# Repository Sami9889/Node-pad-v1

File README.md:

# NodePad

> A tiny, cheap, more-powerful-than-a-Pi homelab node.
> Radxa CM5 (RK3588S2, 8-core, up to 16 GB RAM) on a **100 × 100 mm** carrier board with the kind of I/O a Pi 5 doesn't give you.

**Status:** Rev 0.1 placement/connectivity audit in progress — **not fabrication-ready; do not order**. See `VERIFICATION.md` for blocking footprint and pin-mapping defects.
**Author:** Samrath "Sami" Singh
**License:** TBD (MIT or CERN-OHL-P recommended if you plan to sell it)

---

## What is it?

A carrier board for the **Radxa CM5** compute module. You skip designing the CPU/RAM/eMMC section (Radxa already did that) and get a compact server-class SBC with I/O aimed at self-hosting, homelab, mini-Kubernetes, edge servers, network appliances, and NAS-lite.

Think of it as a **"buy 4, stack them, run K3s on PoE"** kind of board.

## Why not just buy a Pi 5?

| Feature | Pi 5 | Radxa CM5 + NodePad |
|---|---|---|
| CPU | 4× Cortex-A76 @ 2.4 GHz | **8×** (4×A76 + 4×A55) @ 2.4 GHz |
| GPU | VideoCore VII | **Mali-G610 MP4** (better) |
| NPU | ❌ | **6 TOPS** |
| Max RAM | 16 GB | 16 GB |
| Ethernet | 1× **1 GbE** | 2× **2.5 GbE** |
| NVMe | via HAT | **native M.2 M-key on board** |
| PoE | HAT (~$20) | **on-board (optional-populate)** |
| Boot | microSD | **eMMC on module** (no SD lottery) |

## Killer features (the pitch)

1. **Dual 2.5 GbE** — one built into the CM5, second added via the M.2 E-key slot with a 2.5GbE controller card *or* a discrete PHY on-board. Enough to run this thing as a router or a K3s node with dedicated cluster interconnect.
2. **M.2 M-key NVMe** slot (2280) — real SSDs, no microSD.
3. **PoE+ optional** — populate the PoE PD circuit and power it with a single Ethernet cable. Leave it unpopulated for cheap builds.
4. **USB-C PD input** — programmable trigger negotiates 12V/15V/20V from any PD charger. No barrel jack, no wall wart headache.
5. **100 × 100 mm square** — cheapest JLCPCB tier, fits in a 3D-printed cube smaller than a Pi 5.

## Cost target

| Version | BOM cost (qty 10) | Sell target |
|---|---|---|
| **Base** (no PoE) | ~$40 empty board | **$99** empty / **$189** with CM5 8GB |
| **Full** (with PoE) | ~$55 empty board | **$129** empty / **$219** with CM5 8GB |

Comparable products: Turing Pi 2 ($260, but 4-node), Radxa Rock 5A ($90 SBC, no PoE/NVMe boot), DeskPi Super6C ($200, Pi CM4-only). NodePad's niche = smallest + PoE + cheap single node.

---

## Bill of Materials (JLCPCB / LCSC part numbers)

All parts picked to be **in JLCPCB's Basic or Extended library** so the whole board can be assembled by JLC PCBA (no hand-soldering headaches). Prices approximate as of 2026-07.

### Compute
| Ref | Part | Function | LCSC | Qty | Price ea. |
|---|---|---|---|---|---|
| U1 | Radxa CM5 (8 GB / 64 GB) | System-on-module | — (Radxa direct) | 1 | **$89** |
| J1, J2 | Hirose DF40C-100DS-0.4V | 2× 100-pin SoM connectors | C43880 | 2 | $2.50 |

### Networking
| Ref | Part | Function | LCSC | Qty | Price ea. |
|---|---|---|---|---|---|
| U2 | RTL8125BG | 2.5GbE MAC+PHY (2nd NIC) | C2861126 | 1 | $3.10 |
| J3, J4 | Bel Fuse 0826-1G1T-04-F | RJ45 with integrated magnetics + LEDs, PoE-capable | C516428 | 2 | $2.80 |
| Y1 | 25 MHz TCXO 3.3V 20ppm | RTL8125 clock reference | C1804 | 1 | $0.30 |

### Storage
| Ref | Part | Function | LCSC | Qty | Price ea. |
|---|---|---|---|---|---|
| J5 | M.2 M-key 2280 socket | NVMe SSD slot | C725119 | 1 | $1.20 |
| J6 | M.2 E-key 2230 socket | WiFi/BT card or 2nd NIC | C725118 | 1 | $0.95 |

### Power
| Ref | Part | Function | LCSC | Qty | Price ea. |
|---|---|---|---|---|---|
| U3 | MP2315 | 5V @ 3A buck (main rail from 12V PD) | C89358 | 1 | $0.42 |
| U4 | AP2112K-3.3 | 3.3V @ 600 mA LDO (rail for RTC, aux) | C51118 | 1 | $0.20 |
| U5 | CH224K | USB-C PD sink, programmable 5/9/12/15/20V | C970725 | 1 | $0.55 |
| U6 *(opt)* | MP8007GV | PoE+ PD converter (802.3at, 25W) | C910435 | 1 | $2.80 |
| T1 *(opt)* | 750317847 or eq. | PoE flyback transformer | C — | 1 | $2.20 |

### I/O
| Ref | Part | Function | LCSC | Qty | Price ea. |
|---|---|---|---|---|---|
| J7 | USB-C 16-pin recept. | Power in + USB 2.0 data | C165948 | 1 | $0.35 |
| J8–J11 | USB-A 3.0 vertical | 4× USB 3.0 host ports | C165999 | 4 | $0.55 |
| J12 | HDMI Type-A | HDMI 2.0 out | C2681 | 1 | $0.60 |
| J13 | 40-pin 2.54 mm header | Pi-compatible GPIO | C124378 | 1 | $0.25 |
| J14 | microSD push-push socket | Boot fallback | C91145 | 1 | $0.45 |
| J15 | 4-pin 2.54 mm header | PWM fan | C124381 | 1 | $0.15 |

### Housekeeping
| Ref | Part | Function | LCSC | Qty | Price ea. |
|---|---|---|---|---|---|
| U7 | DS3231MZ+ | I²C RTC (server needs to know time on cold boot) | C107373 | 1 | $2.10 |
| BT1 | CR2032 SMD holder | RTC coin cell | C70376 | 1 | $0.28 |
| U8, U9 | USBLC6-2SC6 | USB ESD/TVS | C7469 | 2 | $0.16 |
| SW1 | Momentary 6×6 mm tact | Reset button | C318884 | 1 | $0.08 |
| SW2 | Momentary 6×6 mm tact | Boot/recovery button | C318884 | 1 | $0.08 |
| D1–D5 | 0603 green/red LEDs | Power, activity, link, status | C72043 | 5 | $0.03 |
| — | Passives (R, C, L, ferrites) | ~120 in total, 0402/0603 | JLC Basic | — | ~$3 total |

### PCB
| Item | Spec | Price (qty 10 at JLCPCB) |
|---|---|---|
| 4-layer PCB, 100 × 100 mm, ENIG, black soldermask | Standard stackup, 1 oz Cu | ~$25 total ($2.50/board) |
| JLC PCBA (all SMD assembled) | 1-side, standard | ~$8/board |

### Rolled-up cost per finished board (qty 10)

| Version | PCB | PCBA | Components (per board) | **Empty PCB total** | Add CM5 8GB | **All-in** |
|---|---|---|---|---|---|---|
| Base (no PoE) | $2.50 | $8 | ~$26 | **~$36.50** | +$89 | **$125.50** |
| Full (with PoE) | $2.50 | $9 | ~$32 | **~$43.50** | +$89 | **$132.50** |

Room to sell base @ **$99 (empty PCB only)** or **$199 (with 8GB CM5 pre-installed)** and still keep ~40% margin. 🎯

---

## Block diagram

```
                        ┌──────────────────────────────────┐
                        │      Radxa CM5 (RK3588S2)        │
                        │  8-core • 8GB LPDDR4X • 64GB eMMC│
                        │  Native: 1 GbE, HDMI, USB3.0,    │
                        │  PCIe 2.1 x1, MIPI-DSI/CSI, GPIO │
                        └──┬───┬───┬───┬───┬───┬───┬───────┘
                           │   │   │   │   │   │   │
              ┌────────────┘   │   │   │   │   │   └──────────────┐
              │                │   │   │   │   │                  │
        ┌─────▼─────┐    ┌─────▼─┐ │   │   │ ┌─▼──────┐   ┌───────▼─────┐
        │ RTL8125BG │    │ RJ45  │ │   │   │ │ HDMI 2.0│   │ 40-pin GPIO │
        │  2.5 GbE  │◄──►│ #1 PoE│ │   │   │ └─────────┘   │  Pi-compat  │
        │  (2nd NIC)│    │ 1 GbE │ │   │   │               └─────────────┘
        └─────┬─────┘    └───────┘ │   │   │
              │                    │   │   │
         ┌────▼────┐            ┌──▼─┐ │  ┌▼─────────┐
         │  RJ45 #2│            │M.2 │ │  │ 4× USB   │
         │ 2.5 GbE │            │E-key│ │  │ 3.0 A   │
         │ (opt PoE│            │2230 │ │  └──────────┘
         │  input) │            │(WiFi│ │
         └────┬────┘            │/NIC)│ │
              │                 └─────┘ │
         ┌────▼──────┐         ┌────────▼─┐
         │ MP8007 PoE│         │ M.2 M-key│
         │  PD (opt) │         │  2280    │
         └────┬──────┘         │  NVMe    │
              │                └──────────┘
        ┌─────▼─────┐    ┌──────────────┐   ┌───────────┐
        │ CH224K PD │◄───│  USB-C in    │   │ DS3231 RTC│
        │  trigger  │    │ (5/12/20V)   │   │ +CR2032   │
        └─────┬─────┘    └──────────────┘   └───────────┘
              │
        ┌─────▼──────┐
        │ MP2315 buck│──► 5V rail (CM5, USB, fan, etc.)
        │ + AP2112   │──► 3.3V aux (RTC, LEDs, logic)
        └────────────┘
```

## Repo layout (planned)

```
nodepad/
├── README.md                (this file)
├── DESIGN.md                (deep design rationale, pin assignments, DRC rules)
├── BOM.csv                  (machine-readable, for JLC PCBA upload)
├── PCB/                     (KiCad 10 project)
│   ├── NodePad.kicad_pro
│   ├── NodePad.kicad_sch    (multi-sheet: cpu, network, power, io)
│   └── NodePad.kicad_pcb
├── CAD/                     (case: front, back, mount plate)
│   └── nodepad-case.step
├── Production/
│   ├── gerbers.zip
│   ├── bom.csv              (JLC PCBA format)
│   ├── cpl.csv              (component placement)
│   └── assembly-drawings.pdf
├── Firmware/                (bootloader configs, device tree overlay if needed)
└── docs/
    └── quick-start.md
```

---

## Two variants

| | **NodePad** (base) | **NodePad-Net** (networking) |
|---|---|---|
| **Compute** | Radxa CM5 (8-core RK3588S2 + Mali-G610 GPU + 6 TOPS NPU) | Same |
| **Ethernet** | 1× 1 GbE (native) + 1× 2.5 GbE (RTL8125) | 1× 1 GbE + **2× 2.5 GbE** (2× RTL8125) |
| **Fiber** | — | **1× SFP cage** (1G SGMII) |
| **NVMe** | 1× M.2 M-key 2280 | 1× M.2 M-key 2280 |
| **WiFi slot** | 1× M.2 E-key 2230 | ❌ (PCIe1 used for 2nd NIC) |
| **HDMI** | 1× HDMI 2.0 | ❌ (headless appliance) |
| **USB** | 4× USB-A 3.0 (GL3523 hub) | 2× USB-A 3.0 |
| **PoE** | Footprint-only (DNP) | Footprint-only (DNP) |
| **Netlist stats** | 230 comps, 239 nets, 0 ERC errors | 219 comps, 227 nets, 0 ERC errors |
| **Sell target** | $99 empty / $199 with CM5 | $129 empty / $229 with CM5 |

Both share the same 100 × 100 mm 4-layer PCB scaffold; the SKiDL blocks
compose differently to build each variant's netlist.

### About the CPU + GPU

The CPU (8-core Cortex-A76/A55) and GPU (Mali-G610 MP4) live **on the
Radxa CM5 module itself** — we don't design them into the carrier
board. That's the entire point of using a SoM: you buy the pre-built
compute module for $89 and skip the ~$1000-per-chip BGA design effort.
The carrier board's job is just to break out the CM5's I/O to the
connectors, feed it power, and add the peripherals (Ethernet, USB,
NVMe, SFP, etc.).

---

| # | Decision | Choice |
|---|---|---|
| 1 | **PoE** | Footprint-only (populate optional) |
| 2 | **HDMI** | Kept |
| 3 | **2nd 2.5 GbE NIC** | On-board RTL8125BG (biggest diff vs Pi 5) |
| 4 | **USB 3.0 ports** | 4× vertical Type-A (via GL3523 hub) |
| 5 | **License** | CERN-OHL-P v2 |

---

## Next steps (in order)

- [x] Design brief locked
- [x] KiCad 10 project scaffold created (`/PCB/NodePad.kicad_pro`, `.kicad_sch`, `.kicad_pcb`)
- [x] 100 × 100 mm board outline with 4× M2.5 mounting holes
- [x] 4-layer stackup + JLC-tuned design rules + net classes (PCIe / USB3 / Ethernet / HDMI / Power)
- [x] BOM.csv with LCSC part numbers
- [x] LICENSE (CERN-OHL-P v2)
- [ ] Schematic capture — power tree
- [ ] Schematic capture — CM5 SoM connectors + decoupling
- [ ] Schematic capture — RTL8125 NIC + magnetics
- [ ] Schematic capture — M.2 M-key + E-key slots
- [ ] Schematic capture — GL3523 USB 3.0 hub + 4× USB-A
- [ ] Schematic capture — HDMI, GPIO header, RTC, buttons, LEDs
- [ ] Schematic capture — PoE section (footprint-only, DNP)
- [ ] ERC clean
- [ ] Footprint assignment (JLC-Basic priority)
- [ ] PCB placement
- [ ] PCB routing (PCIe → USB3 → HDMI → Ethernet → GPIO)
- [ ] DRC clean
- [ ] Gerber + CPL + BOM export
- [ ] Order 5 prototypes from JLCPCB (~$400)
- [ ] Bring-up + rev 2 fixes
- [ ] Sellable rev 2 spin

Realistic total timeline from your side: **~3 months part-time** to a rev-2 sellable board. My share (design + docs) is front-loaded in the first 2–3 weeks.

---

## Honest disclaimer

I can draft the schematic + rough PCB layout in KiCad and give you a starting point you can iterate on. **High-speed routing (2.5GbE differential pairs, PCIe Gen 2, USB 3.0)** benefits massively from human review before you spend money on prototypes — it's not the kind of thing to click "generate" and ship. Plan for at least **one rev-2 spin** to fix the bugs the first prototype reveals. Every serious hardware product does this.

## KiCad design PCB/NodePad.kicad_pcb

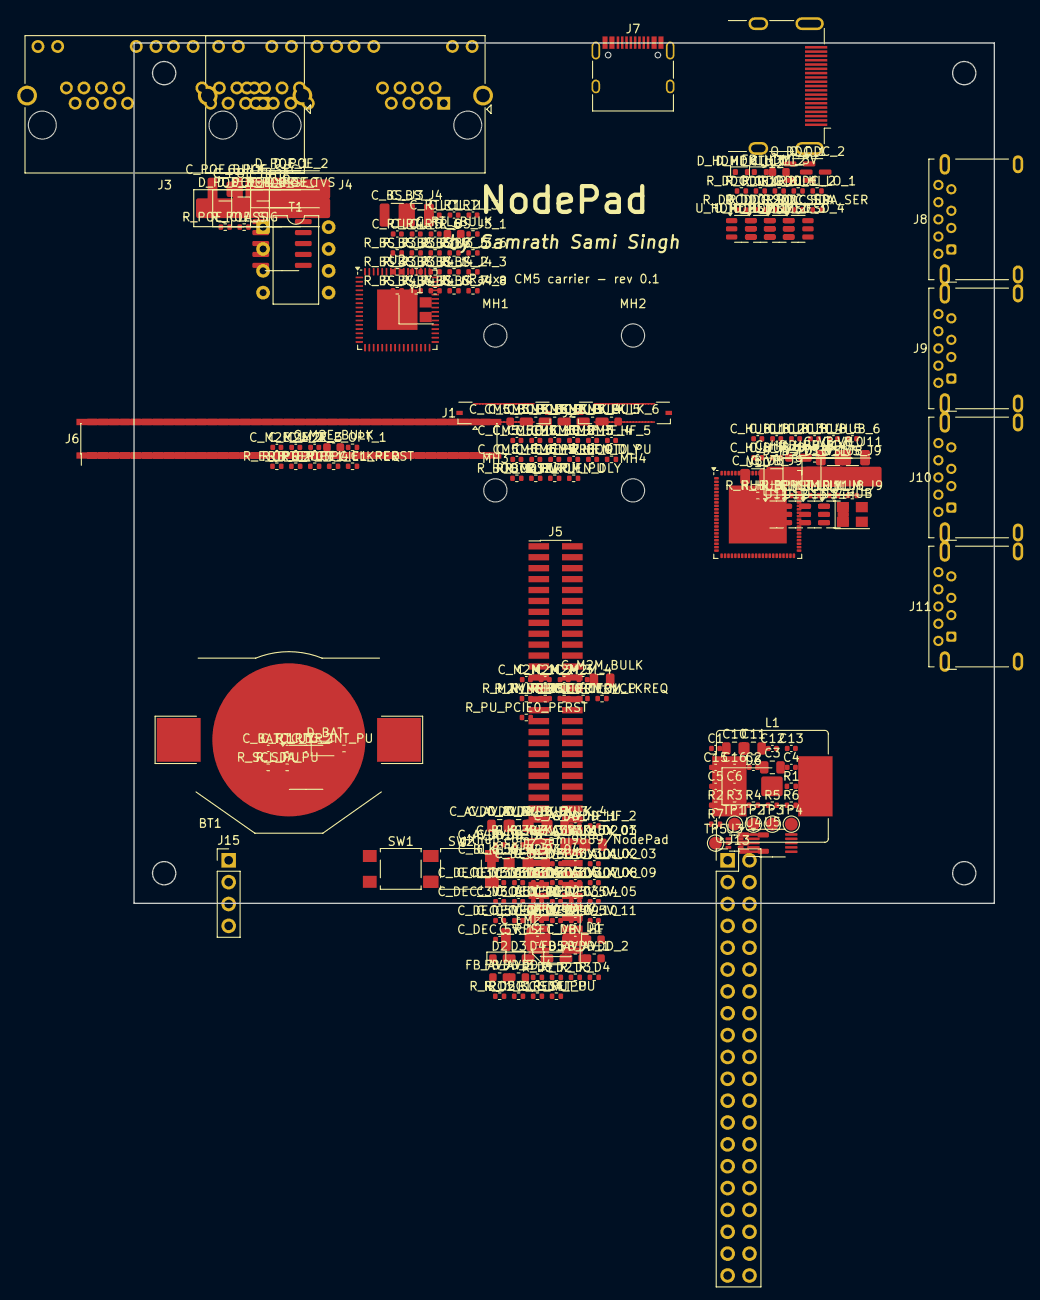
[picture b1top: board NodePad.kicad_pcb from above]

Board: 4 copper layers, 100.0 x 100.0 mm, 249 parts (0 on the bottom side), 94 nets, no tracks yet.

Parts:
BT1: CR2032; BatteryHolder_Keystone_3002_1x2032
C1, C2, C15, C16: 1uF; C_0402_1005Metric
C3, C10, C11: 22uF/25V; C_0805_2012Metric
C4, C13: 100nF; C_0402_1005Metric
C5: 2.2nF; C_0402_1005Metric
C6: 100pF; C_0402_1005Metric
C12: 10uF/16V; C_0402_1005Metric
C_AVDD_BULK_1, C_AVDD_BULK_2, C_AVDD_BULK_3, C_AVDD_BULK_4: 10uF; C_0805_2012Metric
C_AVDD_HF_1, C_AVDD_HF_2, C_AVDD_HF_3, C_AVDD_HF_4: 100nF; C_0402_1005Metric
C_BAT_1: 100nF; C_0402_1005Metric
C_BLK_3V3_AUX_01, C_BLK_3V3_AUX_02, C_BLK_3V3_AUX_03, C_BLK_5V_01, C_BLK_5V_02, C_BLK_5V_03, C_BLK_5V_04: 10uF; C_0805_2012Metric
C_BS_J3, C_BS_J4: 1nF/2kV; C_1210_3225Metric
C_CM5_BULK_1, C_CM5_BULK_2, C_CM5_BULK_3, C_CM5_BULK_4, C_CM5_BULK_5, C_CM5_BULK_6: 10uF; C_0603_1608Metric
C_CM5_HF_1, C_CM5_HF_2, C_CM5_HF_3, C_CM5_HF_4, C_CM5_HF_5, C_CM5_HF_6, C_CM5_HF_7, C_CM5_HF_8, C_CM5_HF_9, C_CM5_HF_10: 100nF; C_0402_1005Metric
C_DEC_3V3_AUX_01, C_DEC_3V3_AUX_02, C_DEC_3V3_AUX_03, C_DEC_3V3_AUX_04, C_DEC_3V3_AUX_05, C_DEC_3V3_AUX_06, C_DEC_3V3_AUX_07, C_DEC_3V3_AUX_08, C_DEC_3V3_AUX_09, C_DEC_3V3_AUX_10, C_DEC_5V_01, C_DEC_5V_02, C_DEC_5V_03, C_DEC_5V_04, C_DEC_5V_05, C_DEC_5V_06, C_DEC_5V_07, C_DEC_5V_08, C_DEC_5V_09, C_DEC_5V_10, C_DEC_5V_11, C_DEC_5V_12: 100nF; C_0402_1005Metric
C_EMI: 1nF/2kV; C_1210_3225Metric
C_HUB_1, C_HUB_2, C_HUB_3, C_HUB_4, C_HUB_5, C_HUB_6, C_HUB_7, C_HUB_8: 100nF; C_0402_1005Metric
C_HUB_BULK: 10uF; C_0603_1608Metric
C_HUB_LDO: 4.7uF; C_0603_1608Metric
C_M2E_1, C_M2E_2, C_M2E_3, C_M2M_1, C_M2M_2, C_M2M_3, C_M2M_4: 100nF; C_0402_1005Metric
C_M2E_BULK: 10uF; C_0603_1608Metric
C_M2M_BULK: 22uF/6.3V; C_0805_2012Metric
C_POE_BULK: 22uF/100V DNP; C_1210_3225Metric
C_POE_HF: 100nF/100V DNP; C_1206_3216Metric
C_POE_SEC: 47uF/25V DNP; C_1210_3225Metric
C_PWR_EN_DLY: 470nF; C_0402_1005Metric
C_RESET_DB: 100nF; C_0402_1005Metric
C_RTC_1: 100nF; C_0402_1005Metric
C_RTC_2: 1uF; C_0402_1005Metric
C_RTL_1, C_RTL_2, C_RTL_3, C_RTL_4, C_RTL_5, C_RTL_6: 100nF; C_0402_1005Metric
C_RTL_BULK: 10uF; C_0603_1608Metric
C_VB_J8, C_VB_J9, C_VB_J10, C_VB_J11: 150uF/6.3V; C_1206_3216Metric
C_VIN_BULK: 47uF/25V; CP_Elec_5x5.4
C_VIN_HF: 100nF; C_0402_1005Metric
D1: Green; LED_0603_1608Metric
D2: Blue; LED_0603_1608Metric
D3, D4: Yellow; LED_0603_1608Metric
D5: Red; LED_0603_1608Metric
D6: SMBJ12A; D_SMB
D_BAT: BAT54; D_SOD-323
D_HDMI_CTL_1, D_HDMI_CTL_2: ESD5Z5.0; D_SOD-523
D_POE_1, D_POE_2, D_POE_3, D_POE_4: HD01-T DNP; D_SMB
D_POE_OR: SS36 DNP; D_SMB
D_POE_SEC: SS36 DNP; D_SMB
D_POE_TVS: SMBJ58A DNP; D_SMB
D_TVS_J8, D_TVS_J9, D_TVS_J10, D_TVS_J11: SMBJ5.0A; D_SMB
FB_AVDD_1, FB_AVDD_2, FB_AVDD_3, FB_AVDD_4: 600R@100MHz; L_0603_1608Metric
FB_HDMI_5V: 600R@100MHz; L_0603_1608Metric
J1: CM5-J1; Hirose_BM24_BM24-40DS-2-0.35V_2x20_P0.35mm_PowerPin2_Vertic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
J2: CM5-J2; Hirose_BM24_BM24-40DS-2-0.35V_2x20_P0.35mm_PowerPin2_Vertic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
J3, J4: RJ45; RJ45_Amphenol_RJHSE538X-02
J5: M.2 M-key 2280; PinHeader_2x38_P1.27mm_Vertical_SMD
J6: M.2 E-key 2230; PinHeader_2x38_P1.27mm_Vertical_SMD
J7: USB-C; USB_C_Receptacle_HRO_TYPE-C-31-M-12
J8, J9, J10, J11: USB3-A; USB3_A_Molex_48393-001
J12: HDMI; HDMI_A_Molex_208658-1001_Horizontal
J13: GPIO40; PinHeader_2x20_P2.54mm_Vertical
J15: Fan; PinHeader_1x04_P2.54mm_Vertical
L1: 4.7uH/3A; L_Bourns_SRR1208_12.7x12.7mm
MH1, MH2, MH3, MH4: M2.5 heatsink; MountingHole_2.7mm_M2.5
Q_DDC_1, Q_DDC_2: BSS138; SOT-23
R1, R2, R6, R7: 10k; R_0402_1005Metric
R3: 0; R_0402_1005Metric
R4: 100k; R_0402_1005Metric
R5: 52.3k; R_0402_1005Metric
R_BOOT0_PU, R_BOOT1_PU, R_BOOT2_PU: 10k; R_0402_1005Metric
R_BS_J3_1, R_BS_J3_2, R_BS_J3_3, R_BS_J3_4, R_BS_J3_5, R_BS_J3_6, R_BS_J3_7, R_BS_J3_8, R_BS_J4_1, R_BS_J4_2, R_BS_J4_3, R_BS_J4_4, R_BS_J4_5, R_BS_J4_6, R_BS_J4_7, R_BS_J4_8: 75; R_0402_1005Metric
R_D1, R_D2, R_D3, R_D4, R_D5: 1k; R_0402_1005Metric
R_DDC_G_1, R_DDC_G_2: 10k; R_0402_1005Metric
R_DDC_HI_1, R_DDC_HI_2: 10k; R_0402_1005Metric
R_DDC_LO_1, R_DDC_LO_2: 10k; R_0402_1005Metric
R_DDC_SCL: 2.2k; R_0402_1005Metric
R_DDC_SCL_SER: 100; R_0402_1005Metric
R_DDC_SDA: 2.2k; R_0402_1005Metric
R_DDC_SDA_SER: 100; R_0402_1005Metric
R_E_OPT_1, R_E_OPT_2, R_E_OPT_3, R_E_OPT_4: 0/DNP; R_0402_1005Metric
R_HUB_BP: 10k; R_0402_1005Metric
R_HUB_RST: 10k; R_0402_1005Metric
R_I2C1_SCL_PU, R_I2C1_SDA_PU: 4.7k; R_0402_1005Metric
R_ILIM_J8, R_ILIM_J9, R_ILIM_J10, R_ILIM_J11: 30k; R_0402_1005Metric
R_INT_PU: 10k; R_0402_1005Metric
R_M2M_PERST: 10k; R_0402_1005Metric
R_MASKROM_PU: 10k; R_0402_1005Metric
R_NVME_ACT_PU: 10k; R_0402_1005Metric
R_PCIE0_TERM_N, R_PCIE0_TERM_P: 49.9 DNP; R_0402_1005Metric
R_POE_CLASS: 12.5 DNP; R_0402_1005Metric
R_POE_SIG: 25k DNP; R_0402_1005Metric
R_PU_PCIE0_CLKREQ, R_PU_PCIE0_PERST, R_PU_PCIE1_CLKREQ, R_PU_PCIE1_PERST: 10k; R_0402_1005Metric
R_PWR_EN_DLY: 100k; R_0402_1005Metric
R_RESET_PU: 10k; R_0402_1005Metric
R_SCL_PU: 4.7k; R_0402_1005Metric
R_SDA_PU: 4.7k; R_0402_1005Metric
SW1: RESET; SW_SPST_TL3305A
SW2: BOOT; SW_SPST_TL3305A
T1: 750317847 DNP; DIP-8_W7.62mm
TP1, TP2, TP3, TP4, TP5: TP; TestPoint_Pad_D1.5mm
U2: RTL8125BG; QFN-64-1EP_9x9mm_P0.5mm_EP4.7x4.7mm
U3: MP2315; SOT-563
U4: AP2112K-3.3; SOT-23-5
U5: CH224K; VSSOP-10_3x3mm_P0.5mm
U6: MP8007 DNP; SOIC-16_3.9x9.9mm_P1.27mm
U7: DS3231MZ+; SOIC-8_3.9x4.9mm_P1.27mm
U10: GL3523; ArtInChip_QFN-88-1EP_10x10mm_P0.4mm_EP6.74x6.74mm
U11, U12, U13, U14: TPS2553; SOT-23-6
U_HDMI_ESD_1, U_HDMI_ESD_2, U_HDMI_ESD_3, U_HDMI_ESD_4: USBLC6-2SC6; SOT-23-6
Y1: 25MHz TCXO; Crystal_SMD_3225-4Pin_3.2x2.5mm
Y_HUB: 25MHz; Crystal_SMD_3225-4Pin_3.2x2.5mm

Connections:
+3V3_AUX: C_BLK_3V3_AUX_01.1, C_BLK_3V3_AUX_02.1, C_BLK_3V3_AUX_03.1, C_DEC_3V3_AUX_01.1, C_DEC_3V3_AUX_02.1, C_DEC_3V3_AUX_03.1, C_DEC_3V3_AUX_04.1, C_DEC_3V3_AUX_05.1, C_DEC_3V3_AUX_06.1, C_DEC_3V3_AUX_07.1, C_DEC_3V3_AUX_08.1, C_DEC_3V3_AUX_09.1, C_DEC_3V3_AUX_10.1, C_HUB_1.1, C_HUB_2.1, C_HUB_3.1, C_HUB_4.1, C_HUB_5.1, C_HUB_6.1, C_HUB_7.1, C_HUB_8.1, C_HUB_BULK.1, C_M2E_1.1, C_M2E_2.1, C_M2E_3.1, C_M2E_BULK.1, C_M2M_1.1, C_M2M_2.1, C_M2M_3.1, C_M2M_4.1, C_M2M_BULK.1, C_RTC_1.1, C_RTC_2.1, C_RTL_1.1, C_RTL_2.1, C_RTL_3.1, C_RTL_4.1, C_RTL_5.1, C_RTL_6.1, C_RTL_BULK.1, D1.1, FB_AVDD_1.1, FB_AVDD_2.1, FB_AVDD_3.1, FB_AVDD_4.1, J5.69, J5.71, J5.73, J5.75, J6.2, J6.4, J6.72, J6.74, J13.1, J13.17, R_BOOT0_PU.1, R_BOOT1_PU.1, R_BOOT2_PU.1, R_DDC_G_1.1, R_DDC_G_2.1, R_DDC_LO_1.1, R_DDC_LO_2.1, R_HUB_BP.1, R_HUB_RST.1, R_I2C1_SCL_PU.1, R_I2C1_SDA_PU.1, R_INT_PU.1, R_M2M_PERST.1, R_MASKROM_PU.1, R_NVME_ACT_PU.1, R_PU_PCIE0_CLKREQ.1, R_PU_PCIE0_PERST.1, R_PU_PCIE1_CLKREQ.1, R_PU_PCIE1_PERST.1, R_RESET_PU.1, R_SCL_PU.1, R_SDA_PU.1, U2.22, U2.23, U2.30, U2.31, U2.40, U2.41, U2.50, U2.51, U7.2
+3V3_AUX1: C16.1, TP4.1, U4.5
+5V: C_BLK_5V_01.1, C_BLK_5V_02.1, C_BLK_5V_03.1, C_BLK_5V_04.1, C_CM5_BULK_1.1, C_CM5_BULK_2.1, C_CM5_BULK_3.1, C_CM5_BULK_4.1, C_CM5_BULK_5.1, C_CM5_BULK_6.1, C_CM5_HF_1.1, C_CM5_HF_2.1, C_CM5_HF_3.1, C_CM5_HF_4.1, C_CM5_HF_5.1, C_CM5_HF_6.1, C_CM5_HF_7.1, C_CM5_HF_8.1, C_CM5_HF_9.1, C_CM5_HF_10.1, C_DEC_5V_01.1, C_DEC_5V_02.1, C_DEC_5V_03.1, C_DEC_5V_04.1, C_DEC_5V_05.1, C_DEC_5V_06.1, C_DEC_5V_07.1, C_DEC_5V_08.1, C_DEC_5V_09.1, C_DEC_5V_10.1, C_DEC_5V_11.1, C_DEC_5V_12.1, FB_HDMI_5V.1, J13.2, J13.4, J15.2, R_DDC_HI_1.1, R_DDC_HI_2.1, R_DDC_SCL.1, R_DDC_SDA.1, R_PWR_EN_DLY.1, U11.1, U11.3, U12.1, U12.3, U13.1, U13.3, U14.1, U14.3, U_HDMI_ESD_1.5, U_HDMI_ESD_2.5, U_HDMI_ESD_3.5, U_HDMI_ESD_4.5
+5V1: C10.1, C11.1, C12.1, C13.1, C15.1, L1.2, R5.1, TP3.1, U4.1, U4.3
BOBSMITH_J3: C_BS_J3.1, R_BS_J3_1.2, R_BS_J3_2.2, R_BS_J3_3.2, R_BS_J3_4.2, R_BS_J3_5.2, R_BS_J3_6.2, R_BS_J3_7.2, R_BS_J3_8.2
BOBSMITH_J4: C_BS_J4.1, R_BS_J4_1.2, R_BS_J4_2.2, R_BS_J4_3.2, R_BS_J4_4.2, R_BS_J4_5.2, R_BS_J4_6.2, R_BS_J4_7.2, R_BS_J4_8.2
CHASSIS_GND: C_BS_J3.2, C_BS_J4.2
CM5_MASKROM: R_MASKROM_PU.2, SW2.1
CM5_POWER_EN: C_PWR_EN_DLY.1, R_PWR_EN_DLY.2
CM5_RUN_N: C_RESET_DB.1, R_RESET_PU.2, SW1.1
ETH0_CT_A: D_POE_1.1, D_POE_3.2
ETH0_CT_B: D_POE_2.1, D_POE_4.2
ETH0_MDI0_N: J3.2, R_BS_J3_2.1
ETH0_MDI0_P: J3.1, R_BS_J3_1.1
ETH0_MDI1_N: J3.6, R_BS_J3_6.1
ETH0_MDI1_P: J3.3, R_BS_J3_3.1
ETH0_MDI2_N: J3.5, R_BS_J3_5.1
ETH0_MDI2_P: J3.4, R_BS_J3_4.1
ETH0_MDI3_N: J3.8, R_BS_J3_8.1
ETH0_MDI3_P: J3.7, R_BS_J3_7.1
ETH1_LED_ACT: D4.1, U2.20
ETH1_MDI0_N: J4.2, R_BS_J4_2.1, U2.2
ETH1_MDI0_P: J4.1, R_BS_J4_1.1, U2.1
ETH1_MDI1_N: J4.6, R_BS_J4_6.1, U2.5
ETH1_MDI1_P: J4.3, R_BS_J4_3.1, U2.4
ETH1_MDI2_N: J4.5, R_BS_J4_5.1, U2.8
ETH1_MDI2_P: J4.4, R_BS_J4_4.1, U2.7
ETH1_MDI3_N: J4.8, R_BS_J4_8.1, U2.11
ETH1_MDI3_P: J4.7, R_BS_J4_7.1, U2.10
GND: BT1.2, C_AVDD_BULK_1.2, C_AVDD_BULK_2.2, C_AVDD_BULK_3.2, C_AVDD_BULK_4.2, C_AVDD_HF_1.2, C_AVDD_HF_2.2, C_AVDD_HF_3.2, C_AVDD_HF_4.2, C_BAT_1.2, C_BLK_3V3_AUX_01.2, C_BLK_3V3_AUX_02.2, C_BLK_3V3_AUX_03.2, C_BLK_5V_01.2, C_BLK_5V_02.2, C_BLK_5V_03.2, C_BLK_5V_04.2, C_CM5_BULK_1.2, C_CM5_BULK_2.2, C_CM5_BULK_3.2, C_CM5_BULK_4.2, C_CM5_BULK_5.2, C_CM5_BULK_6.2, C_CM5_HF_1.2, C_CM5_HF_2.2, C_CM5_HF_3.2, C_CM5_HF_4.2, C_CM5_HF_5.2, C_CM5_HF_6.2, C_CM5_HF_7.2, C_CM5_HF_8.2, C_CM5_HF_9.2, C_CM5_HF_10.2, C_DEC_3V3_AUX_01.2, C_DEC_3V3_AUX_02.2, C_DEC_3V3_AUX_03.2, C_DEC_3V3_AUX_04.2, C_DEC_3V3_AUX_05.2, C_DEC_3V3_AUX_06.2, C_DEC_3V3_AUX_07.2, C_DEC_3V3_AUX_08.2, C_DEC_3V3_AUX_09.2, C_DEC_3V3_AUX_10.2, C_DEC_5V_01.2, C_DEC_5V_02.2, C_DEC_5V_03.2, C_DEC_5V_04.2, C_DEC_5V_05.2, C_DEC_5V_06.2, C_DEC_5V_07.2, C_DEC_5V_08.2, C_DEC_5V_09.2, C_DEC_5V_10.2, C_DEC_5V_11.2, C_DEC_5V_12.2, C_EMI.1, C_HUB_1.2, C_HUB_2.2, C_HUB_3.2, C_HUB_4.2, C_HUB_5.2, C_HUB_6.2, C_HUB_7.2, C_HUB_8.2, C_HUB_BULK.2, C_HUB_LDO.2, C_M2E_1.2, C_M2E_2.2, C_M2E_3.2, C_M2E_BULK.2, C_M2M_1.2, C_M2M_2.2, C_M2M_3.2, C_M2M_4.2, C_M2M_BULK.2, C_POE_SEC.2, C_PWR_EN_DLY.2, C_RESET_DB.2, C_RTC_1.2, C_RTC_2.2, C_RTL_1.2, C_RTL_2.2, C_RTL_3.2, C_RTL_4.2, C_RTL_5.2, C_RTL_6.2, C_RTL_BULK.2, C_VB_J8.2, C_VB_J9.2, C_VB_J10.2, C_VB_J11.2, C_VIN_BULK.2, C_VIN_HF.2, D_HDMI_CTL_1.2, D_HDMI_CTL_2.2, D_TVS_J8.2, D_TVS_J9.2, D_TVS_J10.2, D_TVS_J11.2, J5.70, J5.72, J5.74, J6.1, J6.7, J6.9, J6.11, J6.15, J6.17, J6.19, J6.25, J6.33, J6.39, J6.45, J6.51, J6.57, J6.63, J6.69, J6.75, J8.4, J8.10, J9.4, J9.10, J10.4, J10.10, J11.4, J11.10, J12.2, J12.5, J12.8, J12.11, J12.17, J12.SH, J13.6, J13.9, J13.14, J13.20, J13.25, J13.30, J13.34, J13.39, J15.1, R_D1.2, R_D2.2, R_D3.2, R_D4.2, R_D5.2, R_ILIM_J8.2, R_ILIM_J9.2, R_ILIM_J10.2, R_ILIM_J11.2, SW1.2, SW2.2, T1.5, U2.3, U2.6, U2.9, U2.12, U2.14, U2.17, U2.24, U2.29, U2.32, U2.39, U2.42, U2.49, U2.52, U2.60, U7.5, U11.2, U12.2, U13.2, U14.2, U_HDMI_ESD_1.2, U_HDMI_ESD_2.2, U_HDMI_ESD_3.2, U_HDMI_ESD_4.2
GND1: C1.2, C2.2, C3.2, C5.2, C6.2, C10.2, C11.2, C12.2, C13.2, C15.2, C16.2, D6.2, J7.A1, J7.A12, J7.B1, J7.B12, J7.S1, R1.2, R2.2, R3.2, R6.2, TP5.1, U3.4, U4.2, U5.8
HDMI_CEC: D_HDMI_CTL_1.1, J12.13
HDMI_CLK_N: J12.12, U_HDMI_ESD_4.3, U_HDMI_ESD_4.4
HDMI_CLK_P: J12.10, U_HDMI_ESD_4.1, U_HDMI_ESD_4.6
HDMI_DDC_SCL: J12.15, R_DDC_LO_2.2, R_DDC_SCL.2
HDMI_DDC_SDA: J12.16, R_DDC_LO_1.2, R_DDC_SDA.2
HDMI_HPD: D_HDMI_CTL_2.1, J12.19
HDMI_TX0_N: J12.9, U_HDMI_ESD_1.3, U_HDMI_ESD_1.4
HDMI_TX0_P: J12.7, U_HDMI_ESD_1.1, U_HDMI_ESD_1.6
HDMI_TX1_N: J12.6, U_HDMI_ESD_2.3, U_HDMI_ESD_2.4
HDMI_TX1_P: J12.4, U_HDMI_ESD_2.1, U_HDMI_ESD_2.6
HDMI_TX2_N: J12.3, U_HDMI_ESD_3.3, U_HDMI_ESD_3.4
HDMI_TX2_P: J12.1, U_HDMI_ESD_3.1, U_HDMI_ESD_3.6
I2C0_SCL: R_SCL_PU.2, U7.8
I2C0_SDA: R_SDA_PU.2, U7.7
unnamed: R1.1, U5.5
unnamed: R2.1, U5.6
unnamed: R3.1, U5.7
unnamed: R4.2, U3.6
unnamed: C4.1, U3.1
unnamed: R5.2, R6.1, U3.5
unnamed: C6.1, R7.1
unnamed: C5.1, R7.2
unnamed: U2.15, Y1.1
unnamed: U2.16, Y1.2
unnamed: R_ILIM_J8.1, U11.6
unnamed: R_ILIM_J9.1, U12.6
unnamed: R_ILIM_J10.1, U13.6
unnamed: R_ILIM_J11.1, U14.6
unnamed: R_POE_CLASS.1, U6.3
unnamed: BT1.1, D_BAT.1
unnamed: D1.2, R_D1.1
unnamed: D2.2, R_D2.1
unnamed: D3.2, R_D3.1
unnamed: D4.2, R_D4.1
unnamed: D5.2, R_D5.1
NVME_ACT_N: D5.1, J5.11, R_NVME_ACT_PU.2
PCIE0_CLKREQ_N: J5.52, R_PU_PCIE0_CLKREQ.2
PCIE0_PERST_N: J5.50, R_M2M_PERST.2, R_PU_PCIE0_PERST.2
PCIE0_REFCLK_N: J5.25, R_PCIE0_TERM_N.1
PCIE0_REFCLK_P: J5.27, R_PCIE0_TERM_P.1
PCIE1_CLKREQ_N: J6.50, R_PU_PCIE1_CLKREQ.2, U2.64
PCIE1_PERST_N: J6.56, R_PU_PCIE1_PERST.2, U2.63
PCIE1_RX_N: R_E_OPT_4.2, U2.59
PCIE1_RX_P: R_E_OPT_3.2, U2.58
PCIE1_TX_N: R_E_OPT_2.2, U2.56
PCIE1_TX_P: R_E_OPT_1.2, U2.55
POE_VIN_POS: C_POE_BULK.1, C_POE_HF.1, D_POE_1.2, D_POE_2.2, D_POE_TVS.1, R_POE_SIG.1, T1.1, U6.1
PoE_GND: C_POE_BULK.2, C_POE_HF.2, D_POE_3.1, D_POE_4.1, D_POE_TVS.2, R_POE_CLASS.2, R_POE_SIG.2, U6.2, U6.4, U6.16
RTC_INT_N: R_INT_PU.2, U7.3
SW_5V: C4.2, L1.1, U3.3
USB_CC1: J7.A5, U5.3
USB_CC2: J7.B5, U5.4
USB_DM1: J7.A7, J7.B7, U5.10
USB_DP1: J7.A6, J7.B6, U5.9
VBUS_J8: C_VB_J8.1, D_TVS_J8.1, J8.1, U11.4
VBUS_J9: C_VB_J9.1, D_TVS_J9.1, J9.1, U12.4
VBUS_J10: C_VB_J10.1, D_TVS_J10.1, J10.1, U13.4
VBUS_J11: C_VB_J11.1, D_TVS_J11.1, J11.1, U14.4
VBUS_USB1: C1.1, D6.1, J7.A4, J7.A9, J7.B4, J7.B9, TP1.1, U5.1
VIN_12V: C_VIN_BULK.1, C_VIN_HF.1, D_POE_OR.2
VIN_12V1: C2.1, C3.1, R4.1, TP2.1, U3.2, U5.2
V_BAT: C_BAT_1.1, D_BAT.2, U7.6
__NC__1: J5.1, J5.2, J5.3, J5.4, J5.5, J5.6, J5.7, J5.8, J5.9, J5.10, J5.12, J5.13, J5.14, J5.15, J5.16, J5.17, J5.18, J5.19, J5.20, J5.21, J5.22, J5.23, J5.24, J5.26, J5.28, J5.30, J5.32, J5.34, J5.36, J5.37, J5.38, J5.39, J5.40, J5.41, J5.42, J5.43, J5.44, J5.45, J5.46, J5.47, J5.48, J5.49, J5.51, J5.53, J5.55, J5.56, J5.57, J5.58, J5.59, J5.60, J5.61, J5.62, J5.63, J5.64, J5.65, J5.66, J5.67, J5.68, J6.3, J6.5, J6.6, J6.8, J6.10, J6.12, J6.13, J6.14, J6.16, J6.18, J6.20, J6.22, J6.24, J6.26, J6.27, J6.28, J6.30, J6.32, J6.34, J6.35, J6.37, J6.40, J6.42, J6.44, J6.47, J6.49, J6.52, J6.53, J6.54, J6.55, J6.58, J6.59, J6.60, J6.61, J6.62, J6.64, J6.65, J6.66, J6.67, J6.68, J6.70, J6.71, J6.73

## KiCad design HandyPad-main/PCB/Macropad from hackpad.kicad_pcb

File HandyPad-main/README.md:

# SamiPad

A clean, minimal, handy macropad by **Samrath "Sami" Singh** for times when 104 keys aren't enough 

*(or just an easier way to copy and paste)* 

---

## Quick Start

1. Hold **BOOT** and plug in your XIAO RP2040.
2. Drop `sami_macropad_default.uf2` onto the `RPI-RP2` drive.
3. Plug it back in. Watch **Samrath "Sami" Singh** scroll across the OLED.

---

## Features

- **OLED display** with an animated **Samrath "Sami" Singh** name banner (plus room for custom info)
- **Rotary encoder and button** for volume adjustment, scrolling, or whatever you want to map it to!
- **7 keys** to map to the shortcuts you desire

---

## Defaults (if you don't want to change anything):

### Keys:

| Row        | Key 1           | Key 2           | Key 3         | Key 4        |
|------------|-----------------|-----------------|---------------|--------------|
| **Top**    | Play/Pause      | Previous Track  | Next Track    | Rotary Encoder In This Spot|
| **Bottom** | Copy (Ctrl+C)   | Paste (Ctrl+V)  | Undo (Ctrl+Z) | Print Screen |

### Encoder:

- **Rotate left** → Volume Down
- **Rotate right** → Volume Up
- **Push** → Mute

---

## What is this?

This is a macropad I, **Samrath "Sami" Singh**, built to assist me at my desk. This device can come in handy whether you're designing something in CAD, working on a PCB, gaming, or really anything you would like to use it for.

## How it works and Issues I Faced

The Xiao RP2040 is mounted on the bottom of the PCB along with the diodes. The rest of the components are on the top. The macropad is running **QMK** for the keymaps, screen, and knob. Pretty obvious, but it uses a matrix layout for the switches. 

When I was designing the PCB I wanted to make this macropad as compact as possible with its current hardware which was challenging. I had to reposition the components several times before I was satisfied. I also spent quite some time in CAD designing this case as I wanted to make it as clean as possible. It took me quite some while to find the right shape and size without making it look awkward.

---

## BOM

- 1x unsoldered Seeed XIAO RP2040
- 7x through-hole 1N4148 Diodes
- 7x MX-Style switches
- 1x EC11 Rotary encoder
- 1x 0.91 inch OLED display *(the pin order is GND-VCC-SCL-SDA, **MAKE SURE YOUR PCB MATCHES**)*
- 7x white blank DSA keycaps
- 6x M3x16mm screws

---

## Renders

---

## Schematic

---

## PCB Layout

---

## Author

**Samrath "Sami" Singh**

- GitHub: [@Sami9889](https://github.com/Sami9889)
- Website: [sami-s.dev](https://sami-s.dev)

---

## Credits

Big shout out to **Hack Club** and the **Hackpad** program for giving me the opportunity to make this macropad.

---

## Disclaimer

This project is open source. If anything you make out of this does not work or has any issues, I sincerely apologize, but at the end of the day **that's on you.**

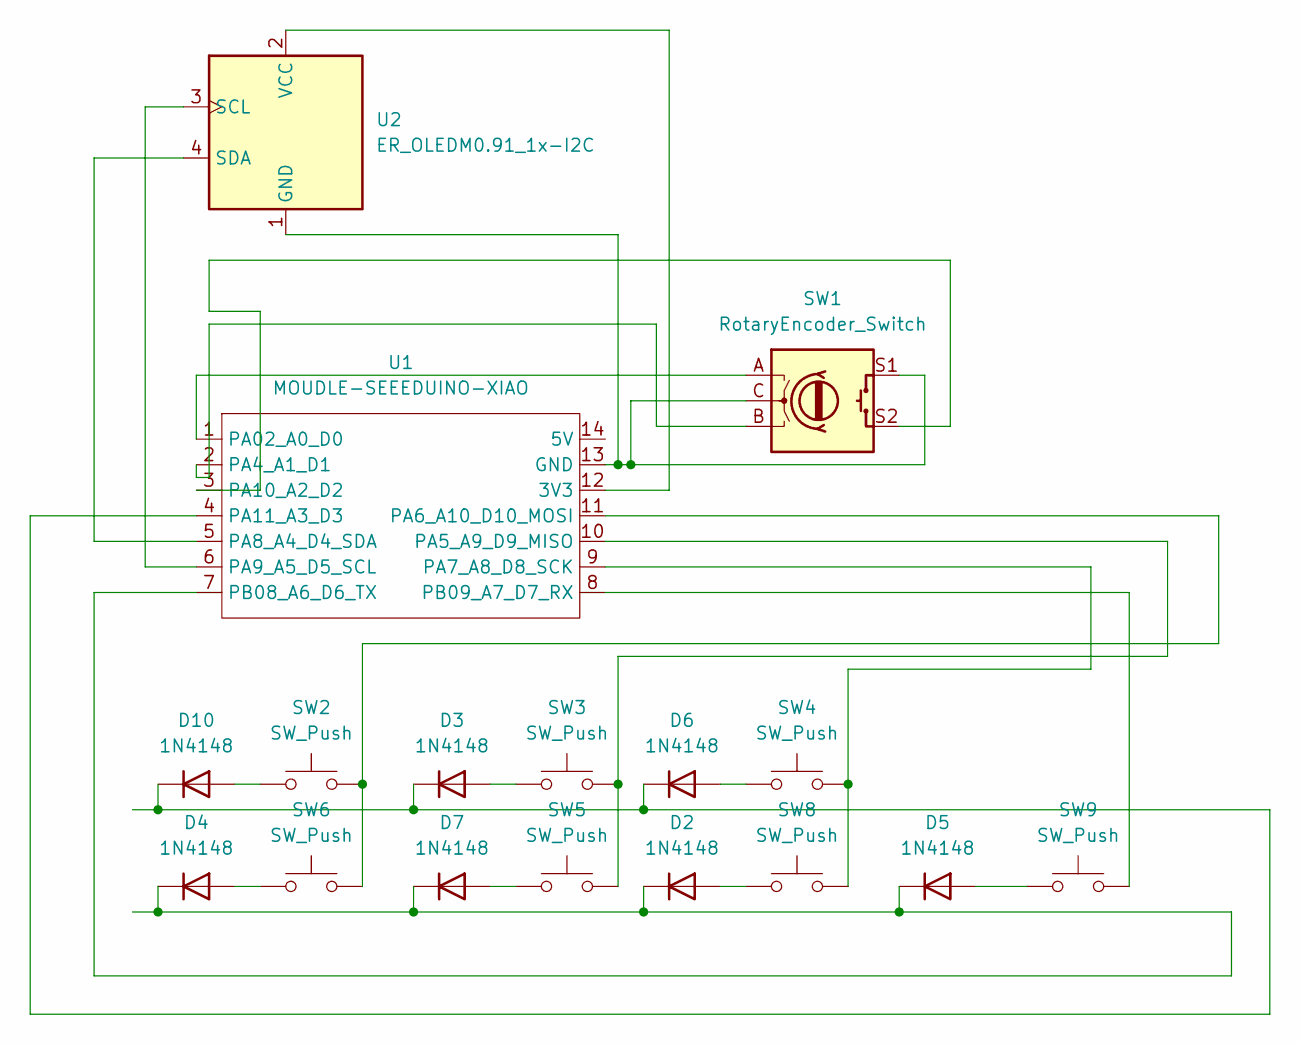
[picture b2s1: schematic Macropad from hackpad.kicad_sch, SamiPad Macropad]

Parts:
D2, D3, D4, D5, D6, D7, D10: 1N4148; D_DO-35_SOD27_P7.62mm_Horizontal
SW1: RotaryEncoder_Switch; RotaryEncoder_Alps_EC11E-Switch_Vertical_H20mm
SW2, SW3, SW4, SW5, SW6, SW8, SW9: SW_Push; SW_Cherry_MX_1.00u_PCB
U1: MOUDLE-SEEEDUINO-XIAO; XIAO-Generic-Hybrid-14P-2.54-21X17.8MM
U2: ER_OLEDM0.91_1x-I2C

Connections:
unnamed: D2.2 (A), SW8.1
unnamed: D2.1 (K), D4.1 (K), D5.1 (K), D7.1 (K), U1.7 (PB08_A6_D6_TX)
unnamed: D3.2 (A), SW3.1
unnamed: D4.2 (A), SW6.1
unnamed: D5.2 (A), SW9.1
unnamed: D6.2 (A), SW4.1
unnamed: D7.2 (A), SW5.1
unnamed: D10.2 (A), SW2.1
unnamed: D3.1 (K), D6.1 (K), D10.1 (K), U1.4 (PA11_A3_D3)
unnamed: U1.12 (3V3), U2.2 (VCC)
unnamed: SW1.C, SW1.S1, U1.13 (GND), U2.1 (GND)
unnamed: SW1.A, U1.1 (PA02_A0_D0)
unnamed: SW1.B, U1.2 (PA4_A1_D1)
unnamed: SW3.2, SW5.2, U1.10 (PA5_A9_D9_MISO)
unnamed: SW2.2, SW6.2, U1.11 (PA6_A10_D10_MOSI)
unnamed: SW4.2, SW8.2, U1.9 (PA7_A8_D8_SCK)
unnamed: U1.5 (PA8_A4_D4_SDA), U2.4 (SDA)
unnamed: U1.6 (PA9_A5_D5_SCL), U2.3 (SCL)
unnamed: SW1.S2, U1.3 (PA10_A2_D2)
unnamed: SW9.2, U1.8 (PB09_A7_D7_RX)

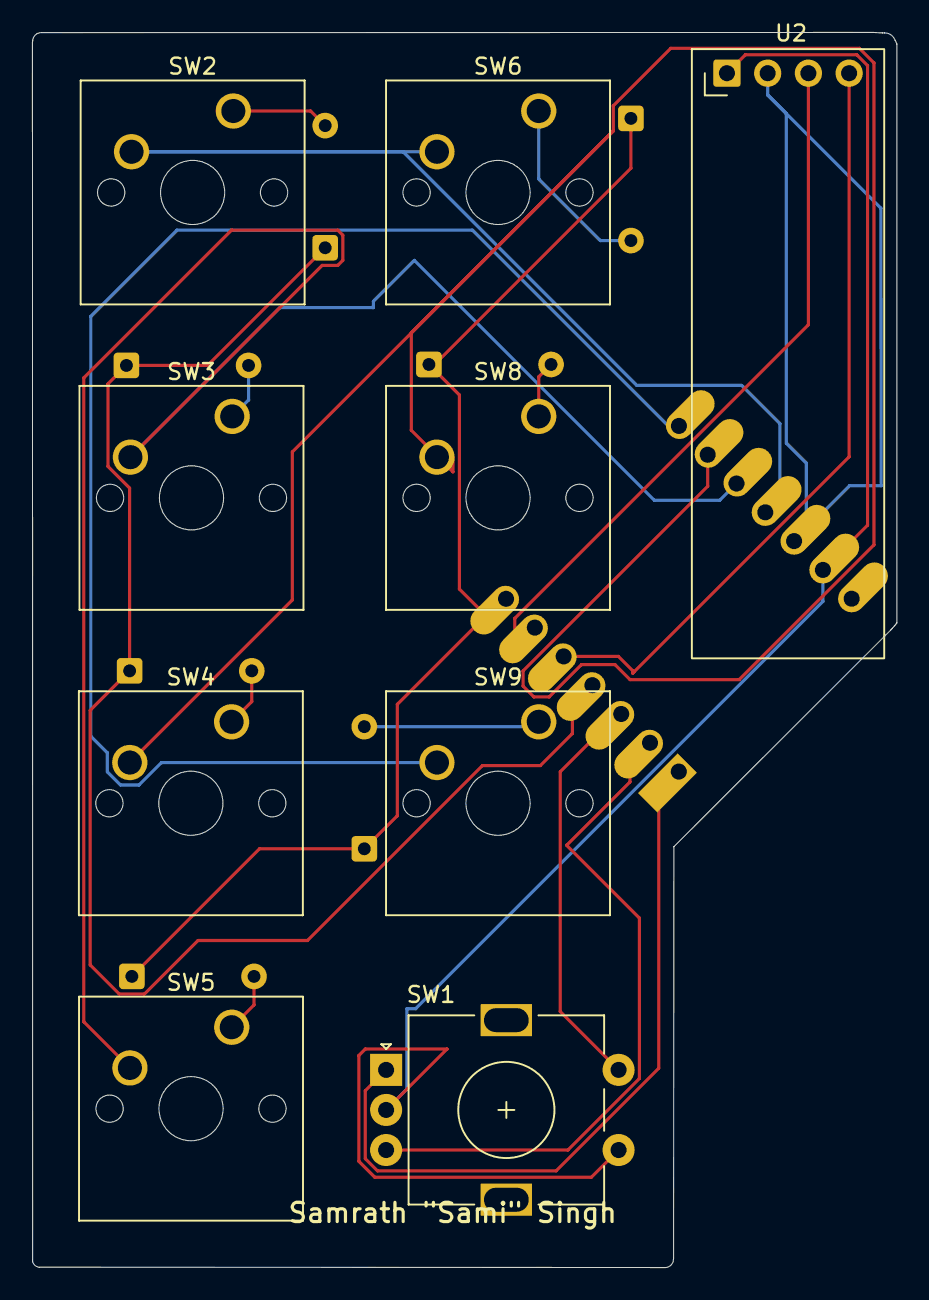
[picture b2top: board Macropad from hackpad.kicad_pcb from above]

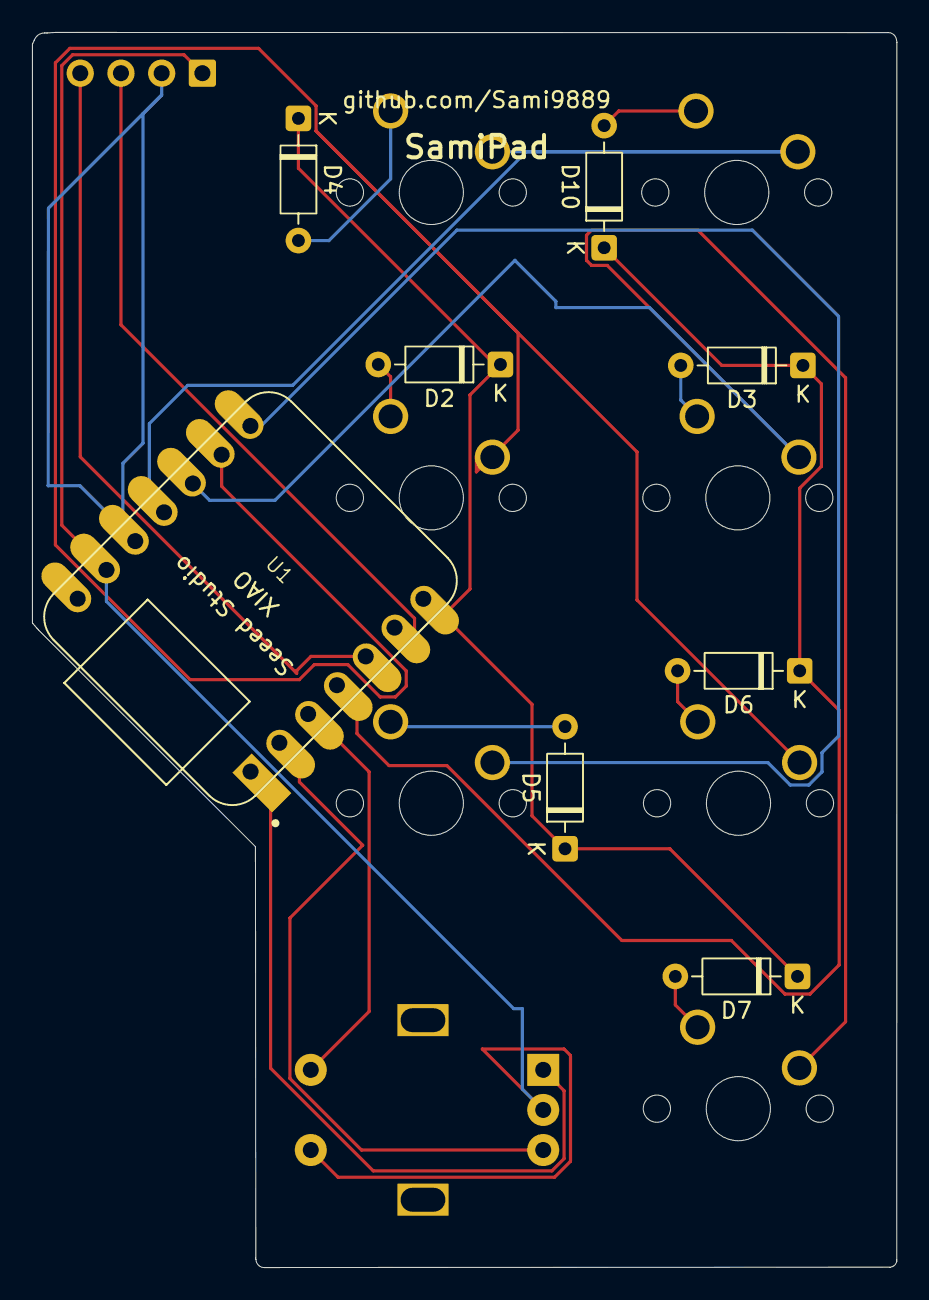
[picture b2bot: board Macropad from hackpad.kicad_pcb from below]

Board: 2 copper layers, 53.9 x 77.0 mm, 17 parts (8 on the bottom side), 20 nets.

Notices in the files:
PCB/NodePad.kicad_pcb:
CERN-OHL-P v2  -  Made with love
